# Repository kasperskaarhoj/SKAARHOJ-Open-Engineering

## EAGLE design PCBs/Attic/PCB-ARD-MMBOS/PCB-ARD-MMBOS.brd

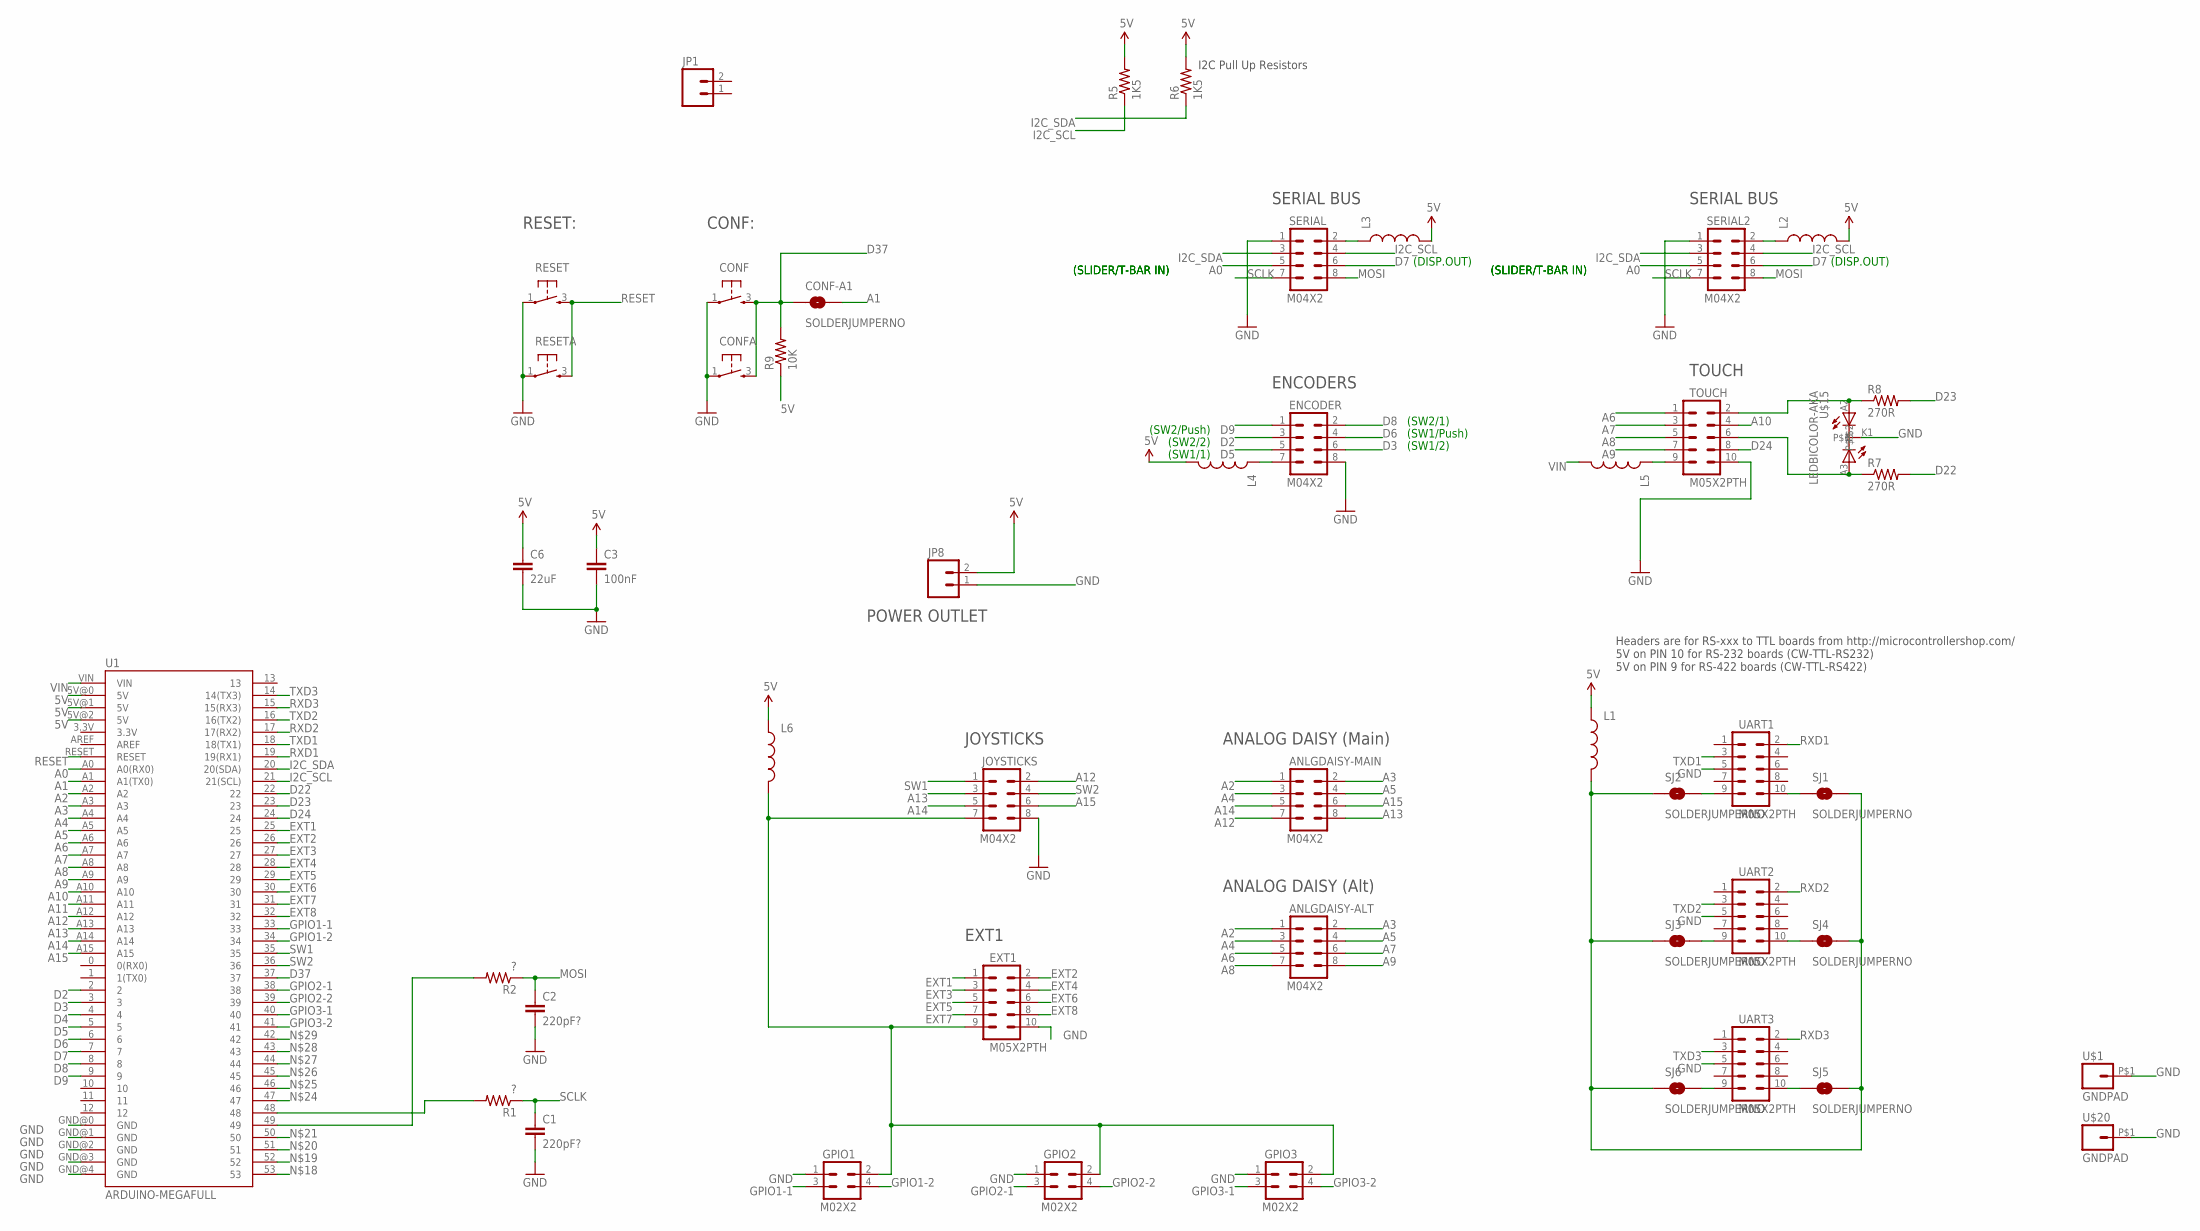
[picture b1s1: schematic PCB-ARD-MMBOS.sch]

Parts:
ANLGDAISY-ALT: M04X2; 2X4
ANLGDAISY-MAIN: M04X2; 2X4
C1, C2: 220pF?; 0603-CAP
C3: 100nF; 0603-CAP
C6: 22uF; 0805
CONF: TAC_SWITCH; PUSHBUTTON
CONF-A1: SOLDERJUMPERNO; SJ_2S-NO
CONFA: TAC_SWITCH; PUSHBUTTON
ENCODER: M04X2; 2X4
EXT1: M05X2PTH; AVR_ICSP
GPIO1, GPIO2, GPIO3: M02X2; 2X2
JOYSTICKS: M04X2; 2X4
JP1: M02PTH; 1X02
JP8: M02PTH4; 1X02_XTRA_BIG
L1, L2, L3, L4, L5, L6: INDUCTOR0805; 0805
R1, R2: ?; 0603-RES
R5, R6: 1K5; 0603-RES
R7, R8: 270R; 0603-RES
R9: 10K; 0603-RES
RESET: TAC_SWITCH; PUSHBUTTON
RESETA: TAC_SWITCH; PUSHBUTTON
SERIAL, SERIAL2: M04X2; 2X4
SJ1, SJ2, SJ3, SJ4, SJ5, SJ6: SOLDERJUMPERNO; SJ_2S-NO
TOUCH: M05X2PTH; AVR_ICSP
U1: ARDUINO-MEGAFULL; ARDUINO_MEGA
U$1, U$20: GNDPAD; 3.2MMPAD
U$15: LEDBICOLOR-AKA; LED5MM-BICOLOR
UART1, UART2, UART3: M05X2PTH; AVR_ICSP

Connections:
5V: C3.1, C6.1, JP8.2, L1.1, L2.2, L3.2, L4.2, L6.1, R5.2, R6.2, R9.1, U1.5V@0 (5V), U1.5V@1 (5V), U1.5V@2 (5V)
A0: SERIAL.5, SERIAL2.5, U1.A0 (A0(RX0))
A1: CONF-A1.2, U1.A1 (A1(TX0))
A2: ANLGDAISY-ALT.1, ANLGDAISY-MAIN.1, U1.A2
A3: ANLGDAISY-ALT.2, ANLGDAISY-MAIN.2, U1.A3
A4: ANLGDAISY-ALT.3, ANLGDAISY-MAIN.3, U1.A4
A5: ANLGDAISY-ALT.4, ANLGDAISY-MAIN.4, U1.A5
A6: ANLGDAISY-ALT.5, TOUCH.1, U1.A6
A7: ANLGDAISY-ALT.6, TOUCH.3, U1.A7
A8: ANLGDAISY-ALT.7, TOUCH.5, U1.A8
A9: ANLGDAISY-ALT.8, TOUCH.7, U1.A9
A10: TOUCH.4, U1.A10
A11: U1.A11
A12: ANLGDAISY-MAIN.7, JOYSTICKS.2, U1.A12
A13: ANLGDAISY-MAIN.8, JOYSTICKS.3, U1.A13
A14: ANLGDAISY-MAIN.5, JOYSTICKS.5, U1.A14
A15: ANLGDAISY-MAIN.6, JOYSTICKS.6, U1.A15
D2: ENCODER.3, U1.2
D3: ENCODER.6, U1.3
D4: U1.4
D5: ENCODER.5, U1.5
D6: ENCODER.4, U1.6
D7: SERIAL.6, SERIAL2.6, U1.7
D8: ENCODER.2, U1.8
D9: ENCODER.1, U1.9
D22: R7.2, U1.22
D23: R8.2, U1.23
D24: TOUCH.8, U1.24
D37: CONF.3, CONF-A1.1, CONFA.3, R9.2, U1.37
EXT1: EXT1.1, U1.25
EXT2: EXT1.2, U1.26
EXT3: EXT1.3, U1.27
EXT4: EXT1.4, U1.28
EXT5: EXT1.5, U1.29
EXT6: EXT1.6, U1.30
EXT7: EXT1.7, U1.31
EXT8: EXT1.8, U1.32
GND: C1.2, C2.2, C3.2, C6.2, CONF.1, CONFA.1, ENCODER.8, EXT1.10, GPIO1.1, GPIO2.1, GPIO3.1, JOYSTICKS.8, JP8.1, RESET.1, RESETA.1, SERIAL.1, SERIAL2.1, TOUCH.10, U1.GND@0 (GND), U1.GND@1 (GND), U1.GND@2 (GND), U1.GND@3 (GND), U1.GND@4 (GND), U$1.P$1, U$15.K1, U$20.P$1, UART1.5, UART2.5, UART3.5
GPIO1-1: GPIO1.3, U1.33
GPIO1-2: GPIO1.4, U1.34
GPIO2-1: GPIO2.3, U1.38
GPIO2-2: GPIO2.4, U1.39
GPIO3-1: GPIO3.3, U1.40
GPIO3-2: GPIO3.4, U1.41
I2C_SCL: R5.1, SERIAL.4, SERIAL2.4, U1.21 (21(SCL))
I2C_SDA: R6.1, SERIAL.3, SERIAL2.3, U1.20 (20(SDA))
MOSI: C2.1, R2.1, SERIAL.8, SERIAL2.8
unnamed: L2.1, SERIAL2.2
unnamed: L3.1, SERIAL.2
unnamed: SJ6.2, UART3.9
unnamed: ENCODER.7, L4.1
unnamed: L5.1, TOUCH.9
unnamed: SJ3.2, UART2.9
unnamed: EXT1.9, GPIO1.2, GPIO2.2, GPIO3.2, JOYSTICKS.7, L6.2
unnamed: L1.2, SJ1.2, SJ2.1, SJ3.1, SJ4.2, SJ5.2, SJ6.1
unnamed: SJ2.2, UART1.9
unnamed: SJ1.1, UART1.10
unnamed: R1.2, U1.48
unnamed: SJ4.1, UART2.10
unnamed: SJ5.1, UART3.10
unnamed: R2.2, U1.49
unnamed: R8.1, TOUCH.2, U$15.A2
unnamed: R7.1, TOUCH.6, U$15.A3
RESET: RESET.3, RESETA.3, U1.RESET
RXD1: U1.19 (19(RX1)), UART1.2
RXD2: U1.17 (17(RX2)), UART2.2
RXD3: U1.15 (15(RX3)), UART3.2
SCLK: C1.1, R1.1, SERIAL.7, SERIAL2.7
SW1: JOYSTICKS.1, U1.35
SW2: JOYSTICKS.4, U1.36
TXD1: U1.18 (18(TX1)), UART1.3
TXD2: U1.16 (16(TX2)), UART2.3
TXD3: U1.14 (14(TX3)), UART3.3
VIN: L5.2, U1.VIN

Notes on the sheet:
JOYSTICKS
EXT1
Headers are for RS-xxx to TTL boards from http://microcontrollershop.com/ 5V on PIN 10 for RS-232 boards (CW-TTL-RS232) 5V on PIN 9 for RS-422 boards (CW-TTL-RS422)
I2C Pull Up Resistors
ENCODERS
SERIAL BUS
TOUCH
(SLIDER/T-BAR IN)
(SW2/Push)
(SW2/2)
(SW1/1)
(SW2/1)
(SW1/Push)
(SW1/2)
(DISP.OUT)
RESET:
CONF:
ANALOG DAISY (Main)
ANALOG DAISY (Alt)
POWER OUTLET

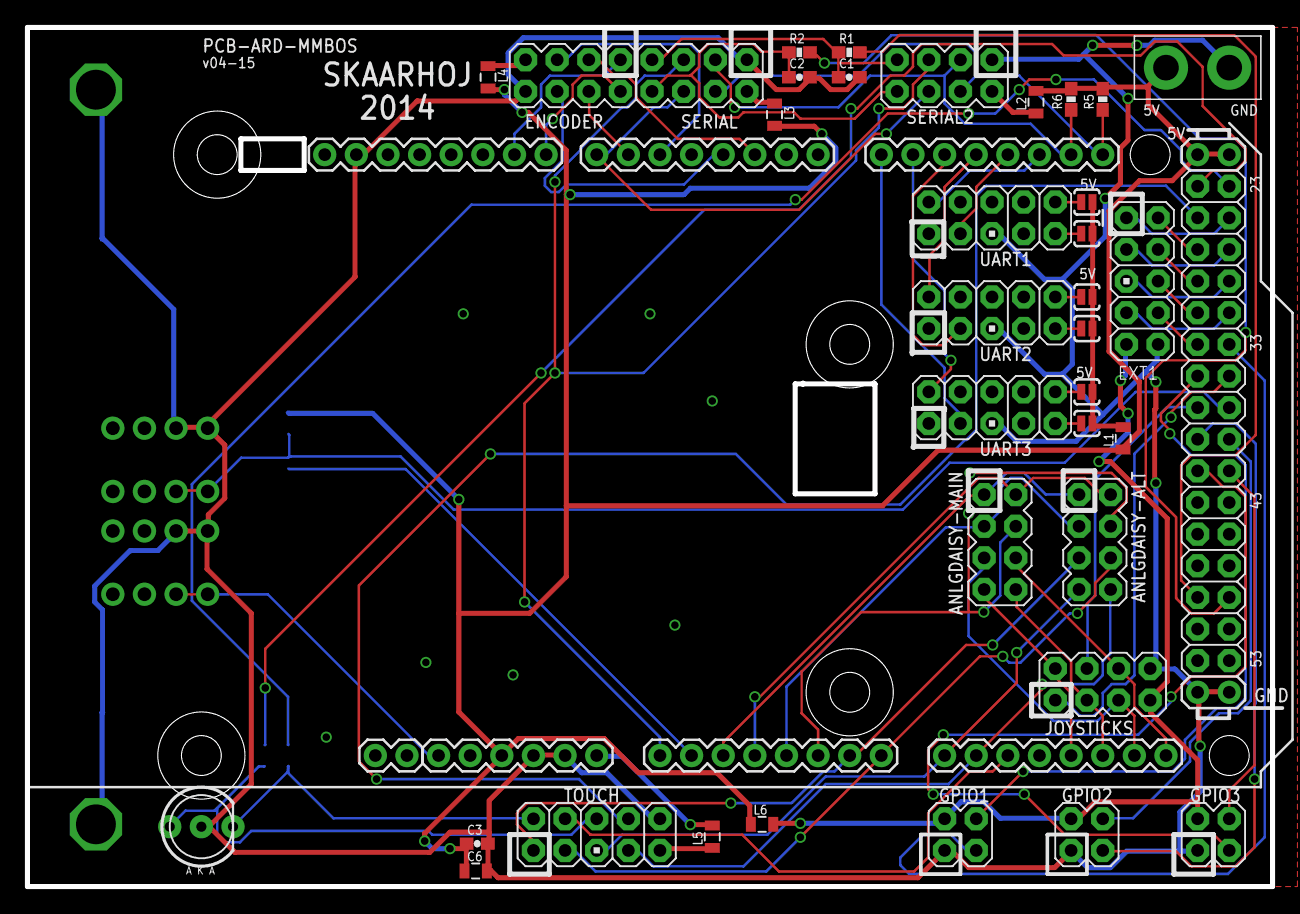
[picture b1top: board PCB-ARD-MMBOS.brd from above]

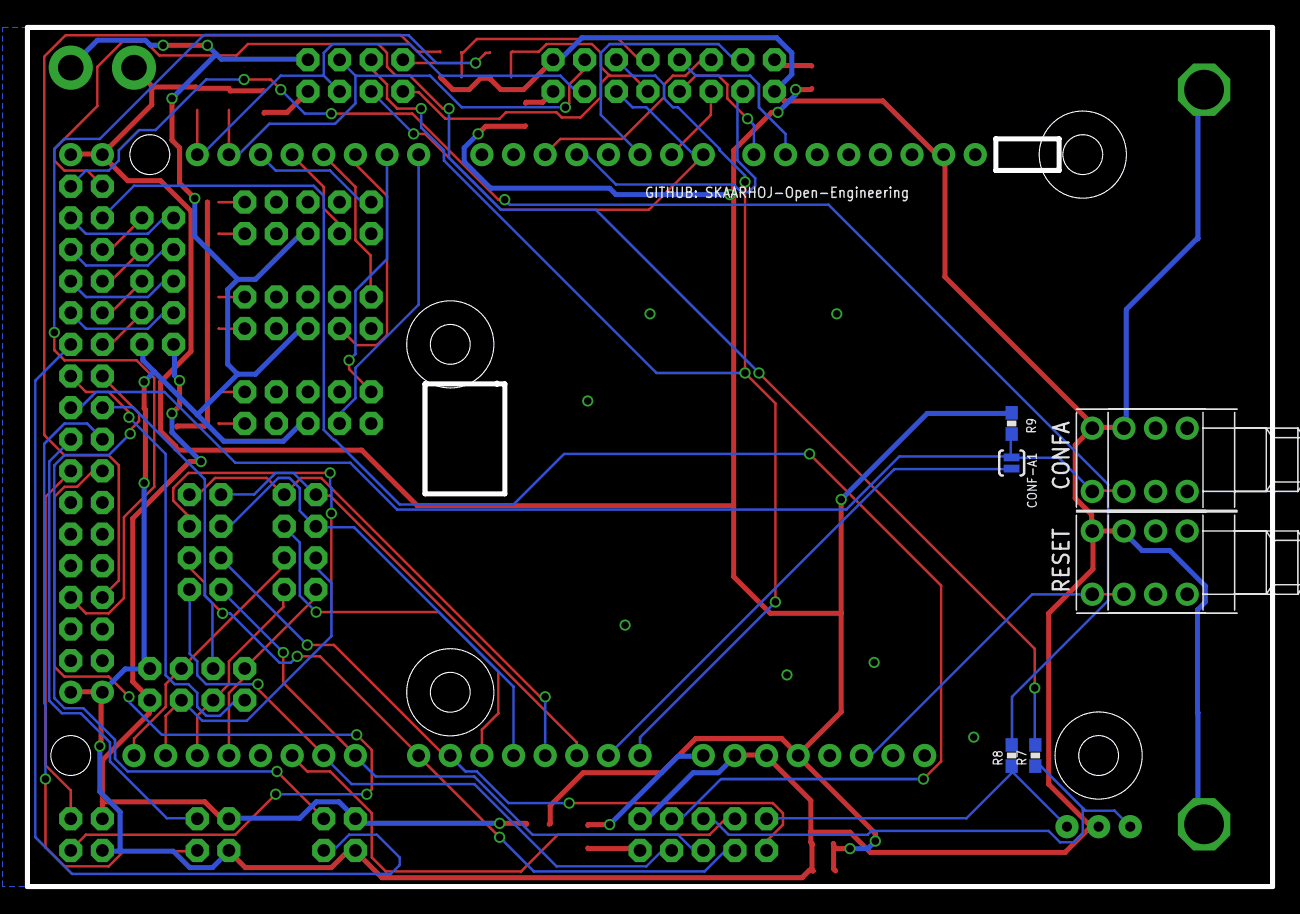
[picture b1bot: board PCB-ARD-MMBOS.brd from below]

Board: 2 copper layers, 100.0 x 69.0 mm, 48 parts (8 on the bottom side), 72 nets.

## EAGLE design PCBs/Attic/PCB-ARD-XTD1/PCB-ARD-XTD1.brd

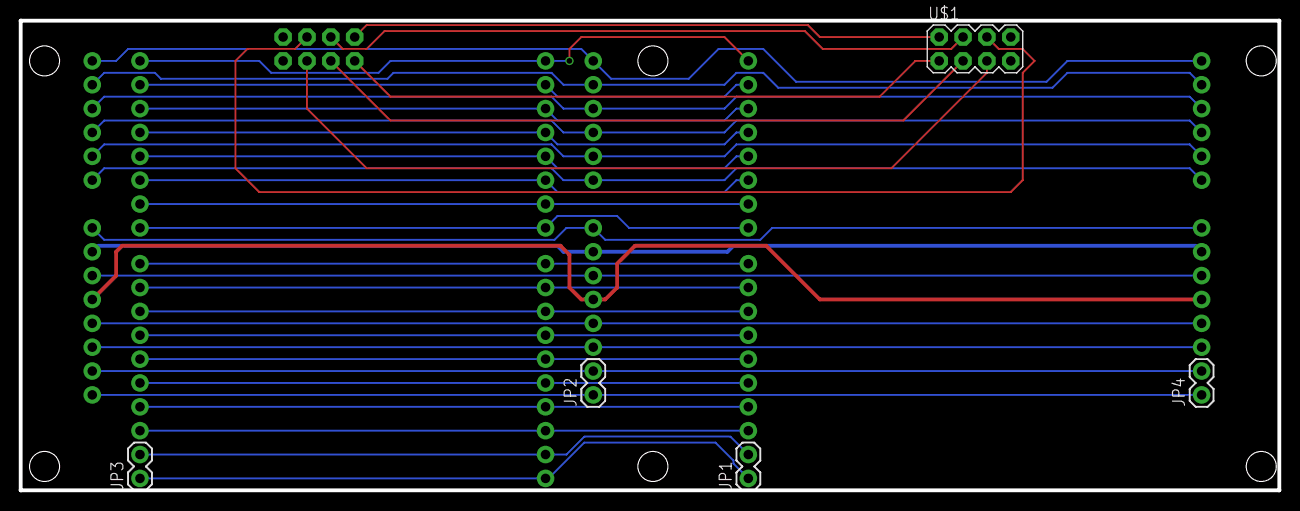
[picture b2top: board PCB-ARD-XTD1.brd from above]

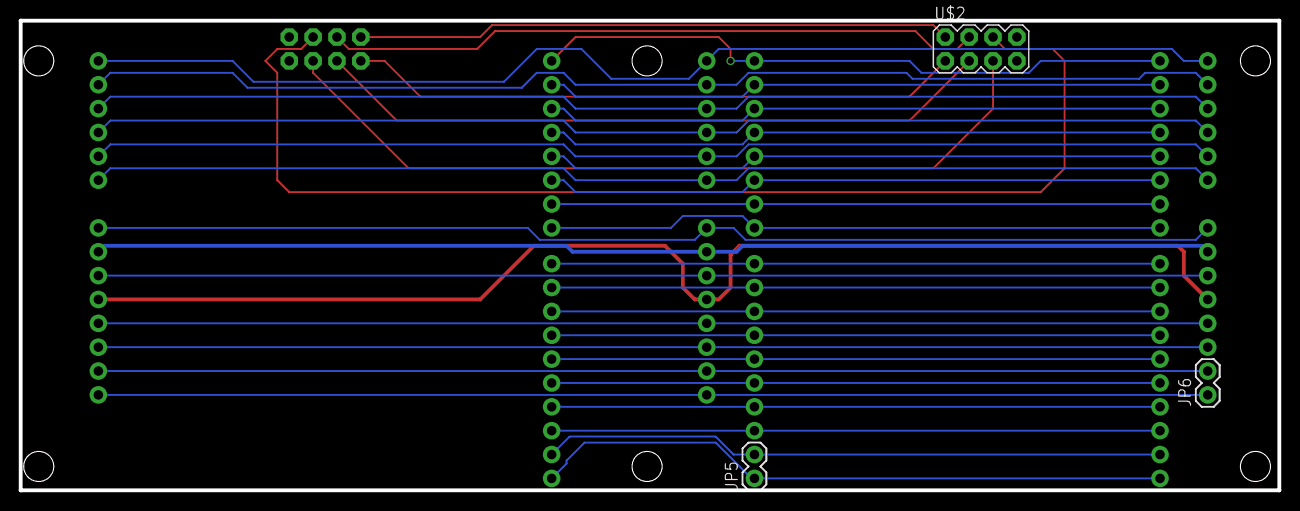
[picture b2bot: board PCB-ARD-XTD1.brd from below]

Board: 2 copper layers, 134.0 x 50.0 mm, 11 parts (4 on the bottom side), 38 nets.

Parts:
JP1, JP2, JP3, JP4, JP5, JP6: 1X02
U1, U2, U3: ARDUINO_SHIELDNO_SILK; DUEMILANOVE_VIAS
U$1, U$2: M04X2; 2X4

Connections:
F1: U1.RX, U2.RX, U3.RX
F2: U1.TX, U2.TX, U3.TX
F3: U1.D2, U2.D2, U3.D2
F4: U1.D3, U2.D3, U3.D3
F5: U1.D4, U2.D4, U3.D4
F6: U1.D5, U2.D5, U3.D5
F7: U1.D6, U2.D6, U3.D6
F8: U1.D7, U2.D7, U3.D7
F9: U1.D8, U2.D8, U3.D8
F10: U1.D9, U2.D9, U3.D9
F11: U1.D10, U2.D10, U3.D10
F12: U1.D11, U2.D11, U3.D11
F13: U1.D12, U2.D12, U3.D12
F14: U1.D13, U2.D13, U3.D13
F15: U1.A0, U2.A0, U3.A0
F16: U1.A1, U2.A1, U3.A1
F17: U1.A2, U2.A2, U3.A2
F18: U1.A3, U2.A3, U3.A3
F19: U1.A4, U2.A4, U3.A4
F20: U1.A5, U2.A5, U3.A5
F21: U1.RES, U2.RES, U3.RES
F22: U1.VIN, U2.VIN, U3.VIN
F23: U1.5V, U2.5V, U3.5V
F24: U1.3.3V, U2.3.3V, U3.3.3V
F25: U1.AREF, U2.AREF, U3.AREF
F26: U1.GND@2, U2.GND@2, U3.GND@2
F27: U1.GND@1, U2.GND@1, U3.GND@1
F28: U1.GND@0, U2.GND@0, U3.GND@0
F29: JP1.2, JP3.2, JP5.2
F30: JP1.1, JP3.1, JP5.1
F31: U$1.1, U$2.1
F32: U$1.3, U$2.3
F33: U$1.5, U$2.5
F35: U$1.2, U$2.2
F36: U$1.4, U$2.4
F37: U$1.6, U$2.6
F39: JP2.2, JP4.2, JP6.2
F40: JP2.1, JP4.1, JP6.1

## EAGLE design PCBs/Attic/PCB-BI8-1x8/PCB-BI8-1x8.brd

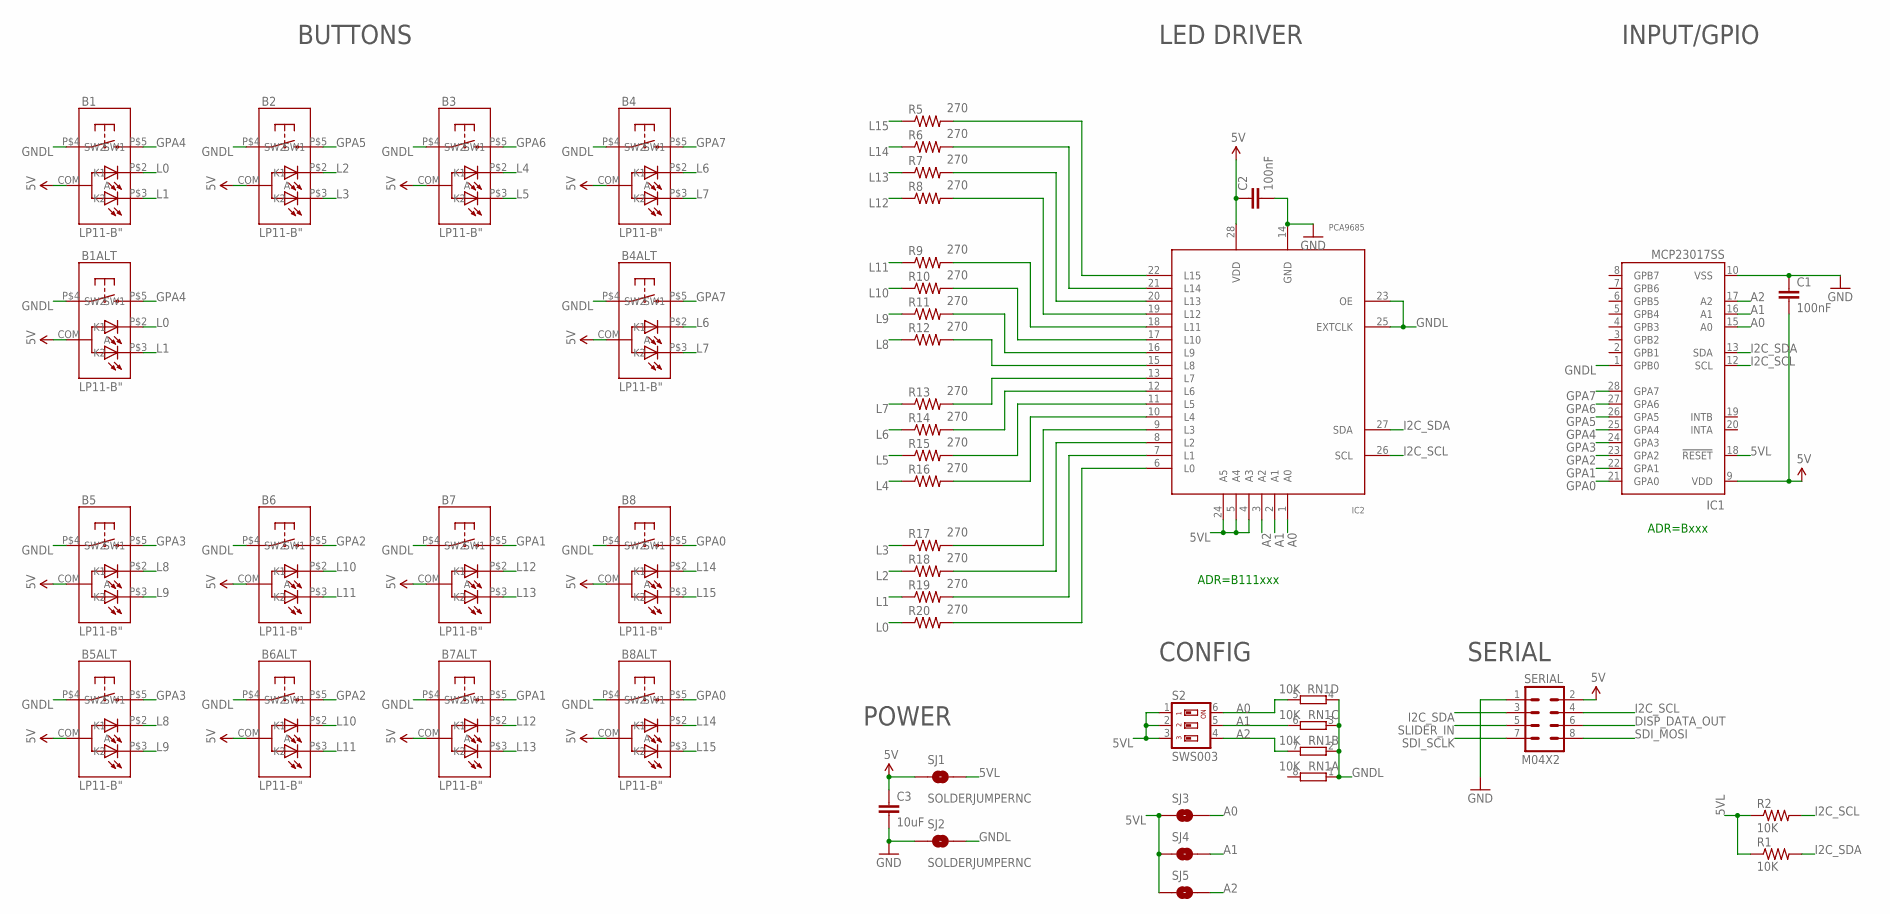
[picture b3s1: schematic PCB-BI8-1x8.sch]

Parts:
B1, B1ALT, B2, B3, B4, B4ALT, B5, B5ALT, B6, B6ALT, B7, B7ALT, B8, B8ALT: LP11-B"; LP11
C1, C2: 100nF; 0603-CAP
C3: 10uF; 0805
IC1: MCP23017SS; SSOP28; MPN MCP23017-E/SS
IC2: PCA9685; TSSOP28
R1, R2: 10K; 0603-RES
R5, R6, R7, R8, R9, R10, R11, R12, R13, R14, R15, R16, R17, R18, R19, R20: 270; 0603-RES
RN1: 10K; CAY16_HAND
S2: SWS003; SMS-003
SERIAL: M04X2; 2X4
SJ1, SJ2, SJ3, SJ4, SJ5: SOLDERJUMPERNC; SJ_2S

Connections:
5V: B1.COM (A), B1ALT.COM (A), B2.COM (A), B3.COM (A), B4.COM (A), B4ALT.COM (A), B5.COM (A), B5ALT.COM (A), B6.COM (A), B6ALT.COM (A), B7.COM (A), B7ALT.COM (A), B8.COM (A), B8ALT.COM (A), C1.2, C2.1, C3.1, IC1.9 (VDD), IC2.28 (VDD), SERIAL.2, SJ1.1
5VL: IC1.18 (!RESET), IC2.4 (A3), IC2.5 (A4), IC2.24 (A5), R1.1, R2.1, S2.1, S2.2, S2.3, SJ1.2, SJ3.1, SJ4.1, SJ5.1
A0: IC1.15 (A0), IC2.1 (A0), RN1.5 (2), S2.6, SJ3.2
A1: IC1.16 (A1), IC2.2 (A1), RN1.6 (2), S2.5, SJ4.2
A2: IC1.17 (A2), IC2.3 (A2), RN1.7 (2), S2.4, SJ5.2
DISP_DATA_OUT: SERIAL.6
GND: C1.1, C2.2, C3.2, IC1.10 (VSS), IC2.14 (GND), SERIAL.1, SJ2.1
GNDL: B1.P$4 (SW1), B1ALT.P$4 (SW1), B2.P$4 (SW1), B3.P$4 (SW1), B4.P$4 (SW1), B4ALT.P$4 (SW1), B5.P$4 (SW1), B5ALT.P$4 (SW1), B6.P$4 (SW1), B6ALT.P$4 (SW1), B7.P$4 (SW1), B7ALT.P$4 (SW1), B8.P$4 (SW1), B8ALT.P$4 (SW1), IC1.1 (GPB0), IC2.23 (OE), IC2.25 (EXTCLK), RN1.1, RN1.2 (1), RN1.3 (1), RN1.4 (1), SJ2.2
GPA0: B8.P$5 (SW2), B8ALT.P$5 (SW2), IC1.21 (GPA0)
GPA1: B7.P$5 (SW2), B7ALT.P$5 (SW2), IC1.22 (GPA1)
GPA2: B6.P$5 (SW2), B6ALT.P$5 (SW2), IC1.23 (GPA2)
GPA3: B5.P$5 (SW2), B5ALT.P$5 (SW2), IC1.24 (GPA3)
GPA4: B1.P$5 (SW2), B1ALT.P$5 (SW2), IC1.25 (GPA4)
GPA5: B2.P$5 (SW2), IC1.26 (GPA5)
GPA6: B3.P$5 (SW2), IC1.27 (GPA6)
GPA7: B4.P$5 (SW2), B4ALT.P$5 (SW2), IC1.28 (GPA7)
I2C_SCL: IC1.12 (SCL), IC2.26 (SCL), R2.2, SERIAL.4
I2C_SDA: IC1.13 (SDA), IC2.27 (SDA), R1.2, SERIAL.3
L0: B1.P$2 (K1), B1ALT.P$2 (K1), R20.1
L1: B1.P$3 (K2), B1ALT.P$3 (K2), R19.1
L2: B2.P$2 (K1), R18.1
L3: B2.P$3 (K2), R17.1
L4: B3.P$2 (K1), R16.1
L5: B3.P$3 (K2), R15.1
L6: B4.P$2 (K1), B4ALT.P$2 (K1), R14.1
L7: B4.P$3 (K2), B4ALT.P$3 (K2), R13.1
L8: B5.P$2 (K1), B5ALT.P$2 (K1), R12.1
L9: B5.P$3 (K2), B5ALT.P$3 (K2), R11.1
L10: B6.P$2 (K1), B6ALT.P$2 (K1), R10.1
L11: B6.P$3 (K2), B6ALT.P$3 (K2), R9.1
L12: B7.P$2 (K1), B7ALT.P$2 (K1), R8.1
L13: B7.P$3 (K2), B7ALT.P$3 (K2), R7.1
L14: B8.P$2 (K1), B8ALT.P$2 (K1), R6.1
L15: B8.P$3 (K2), B8ALT.P$3 (K2), R5.1
unnamed: IC2.13 (L7), R13.2
unnamed: IC2.12 (L6), R14.2
unnamed: IC2.11 (L5), R15.2
unnamed: IC2.10 (L4), R16.2
unnamed: IC2.9 (L3), R17.2
unnamed: IC2.8 (L2), R18.2
unnamed: IC2.7 (L1), R19.2
unnamed: IC2.6 (L0), R20.2
unnamed: IC2.15 (L8), R12.2
unnamed: IC2.16 (L9), R11.2
unnamed: IC2.17 (L10), R10.2
unnamed: IC2.18 (L11), R9.2
unnamed: IC2.19 (L12), R8.2
unnamed: IC2.20 (L13), R7.2
unnamed: IC2.21 (L14), R6.2
unnamed: IC2.22 (L15), R5.2
SDI_MOSI: SERIAL.8
SDI_SCLK: SERIAL.7
SLIDER_IN: SERIAL.5

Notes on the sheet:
ADR=B111xxx
ADR=Bxxx
BUTTONS
LED DRIVER
INPUT/GPIO
POWER
CONFIG
SERIAL

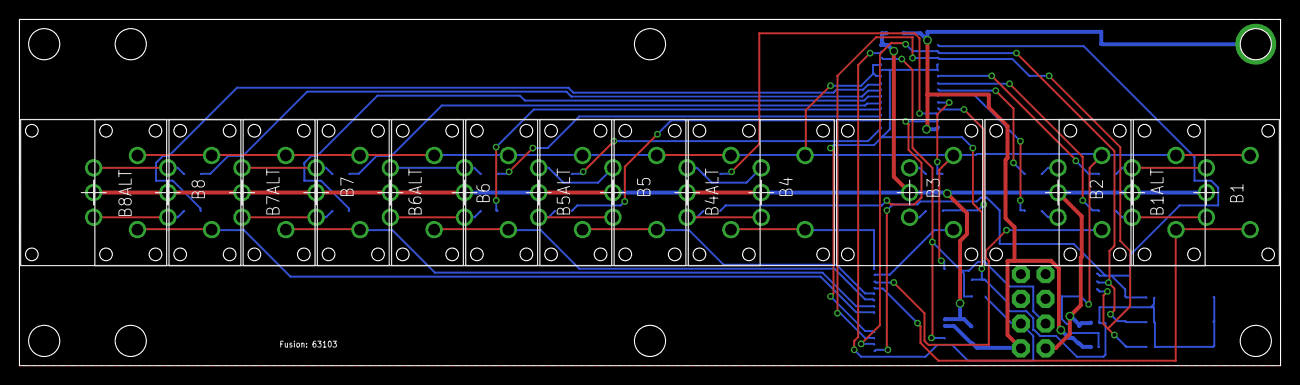
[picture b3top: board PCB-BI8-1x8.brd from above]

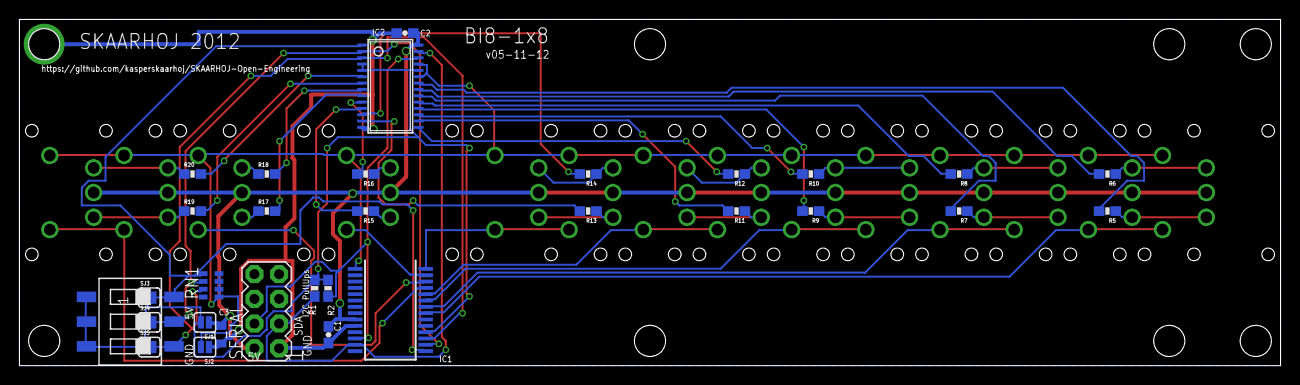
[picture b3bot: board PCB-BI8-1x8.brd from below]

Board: 2 copper layers, 129.5 x 35.6 mm, 45 parts (31 on the bottom side), 49 nets.

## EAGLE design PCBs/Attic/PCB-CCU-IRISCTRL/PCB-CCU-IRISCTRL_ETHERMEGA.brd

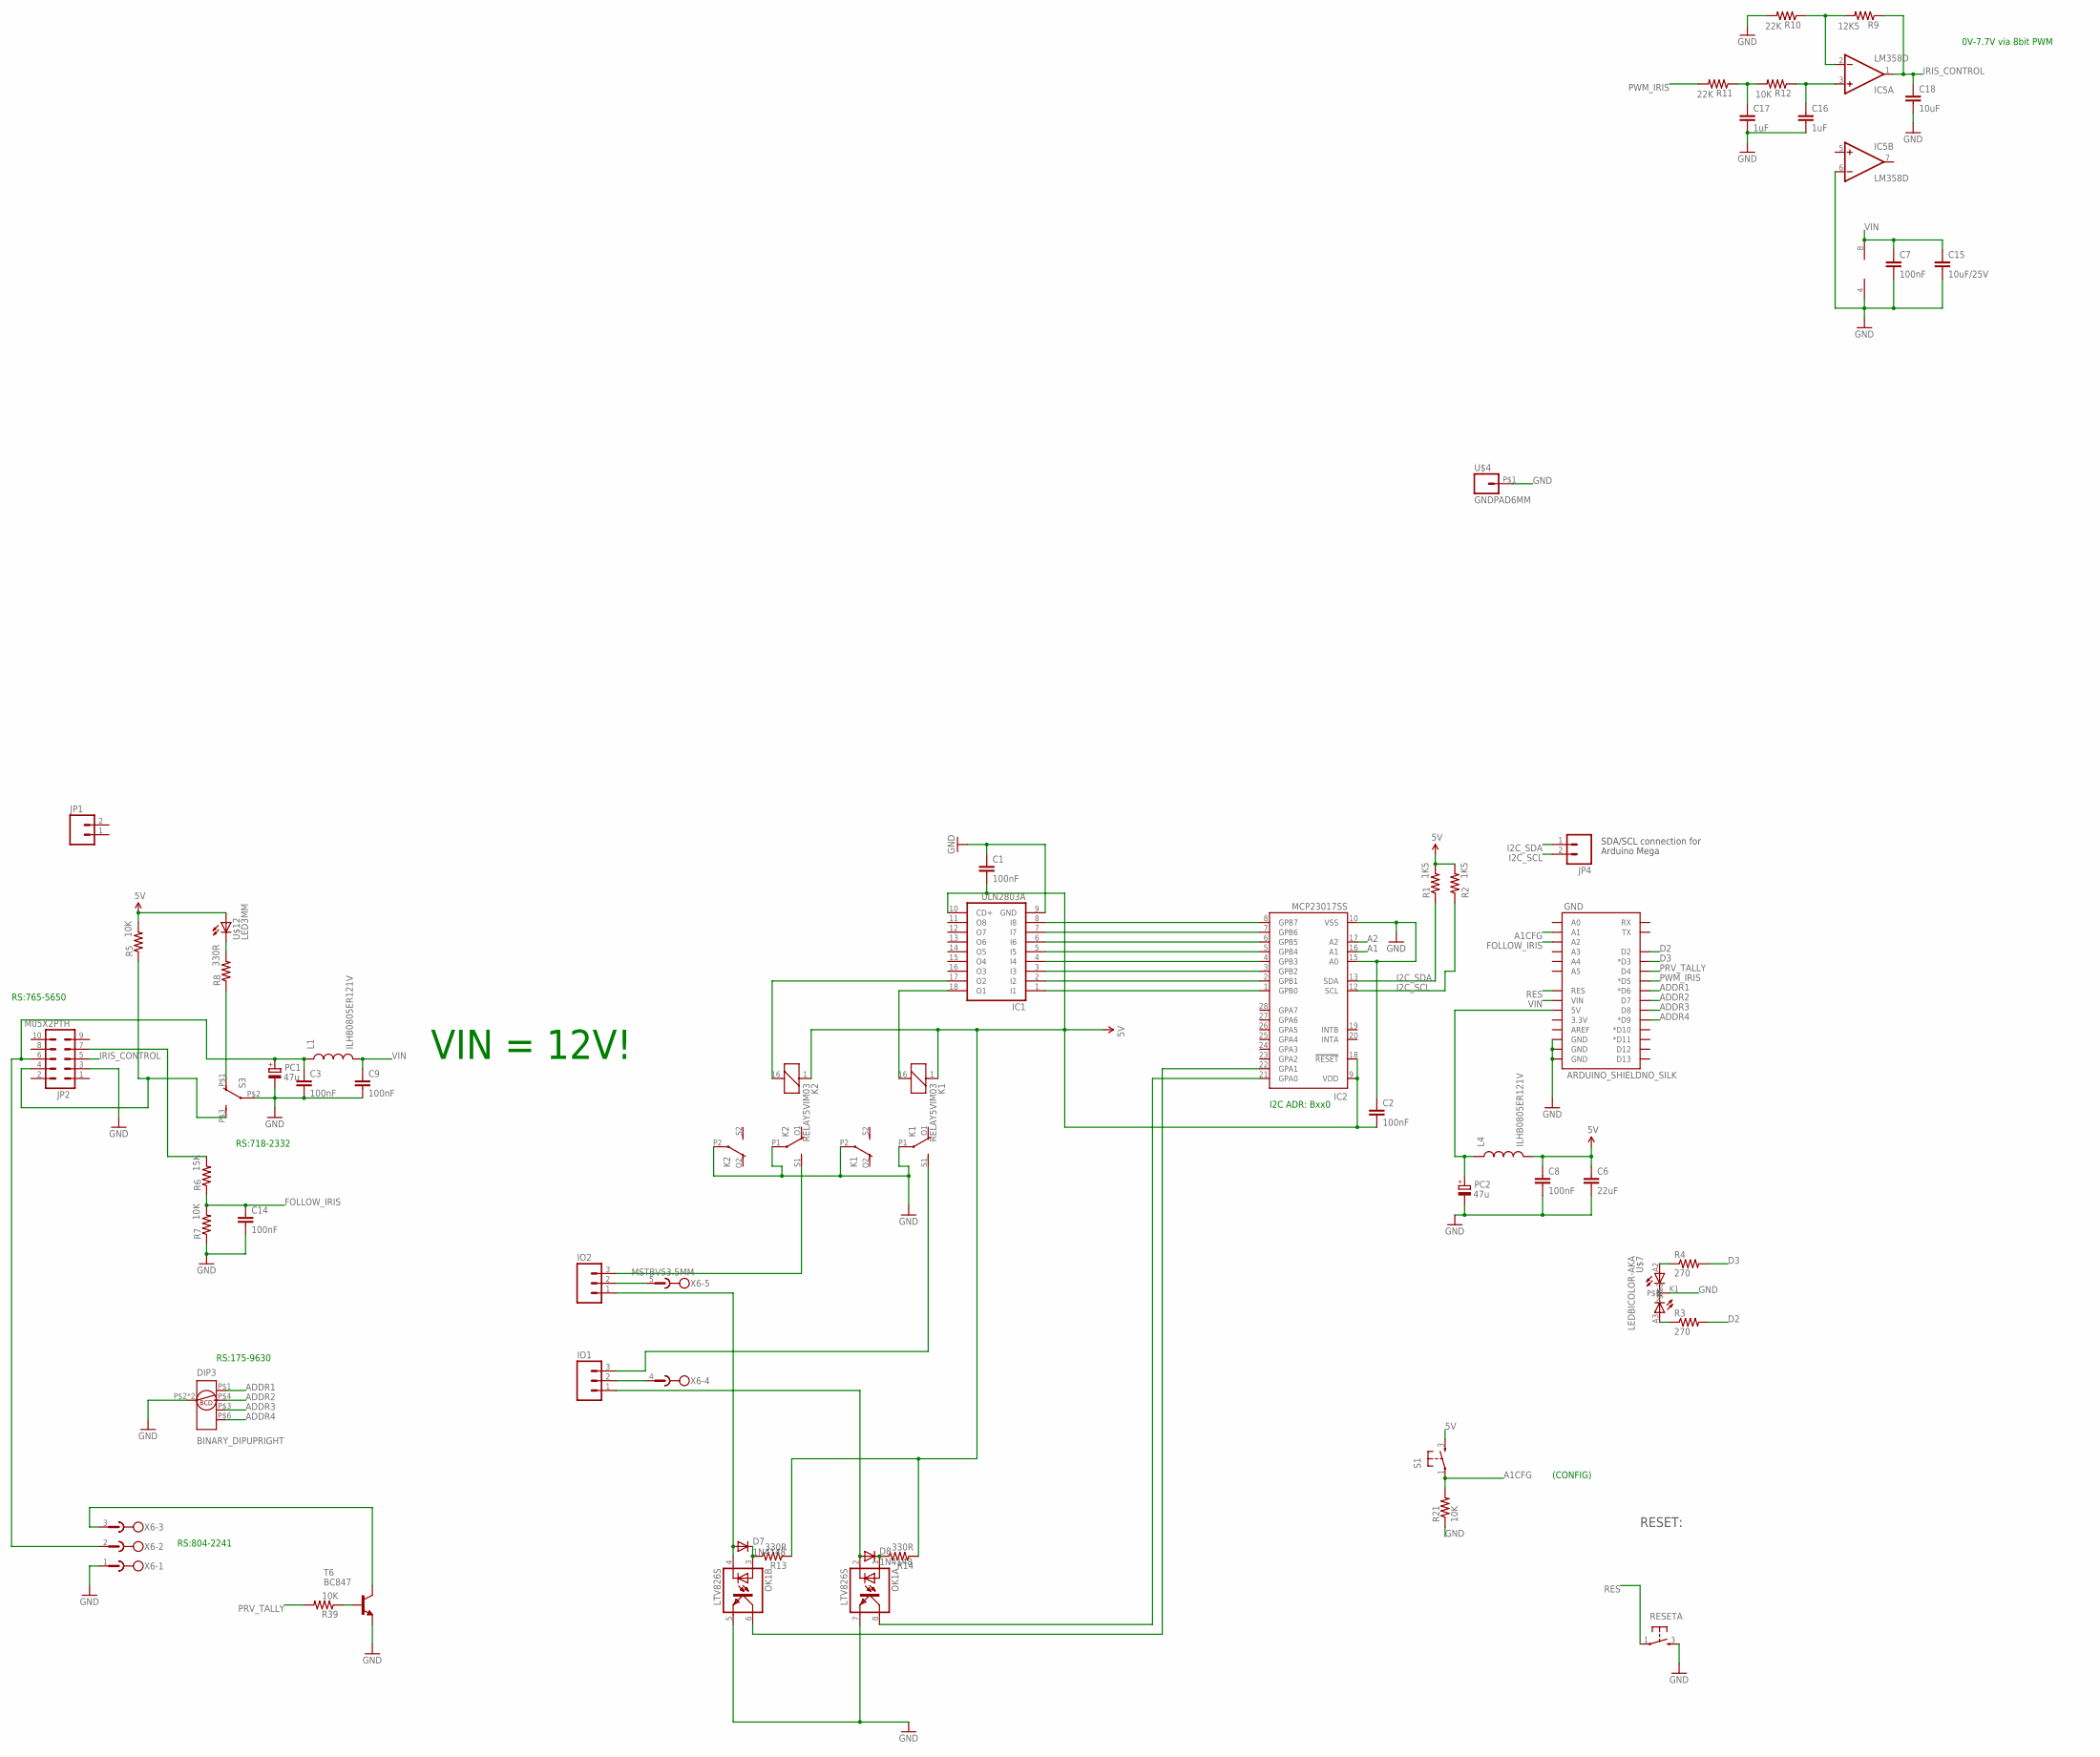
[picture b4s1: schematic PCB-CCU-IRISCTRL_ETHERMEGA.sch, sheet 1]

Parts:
C1: 100nF; 0805
C2, C3, C7, C8, C9, C14: 100nF; 0603-CAP
C6: 22uF; 0805
C15: 10uF/25V; 0805
C16, C17: 1uF; 0805
C18: 10uF; 0805
D7, D8: 1N4148; SOD-323
DIP3: BINARY_DIPUPRIGHT; P65SMT_UPRIGHT_TH
GND: ARDUINO_SHIELDNO_SILK; DUEMILANOVE_VIAS
IC1: ULN2803A; SO18W
IC2: MCP23017SS; SSOP28
IC5: LM358D; SO08
IO1, IO2: M03LOCK; 1X03_LOCK
JP1, JP4: M02PTH; 1X02
JP2: M05X2PTH; AVR_ICSP
K1, K2: RELAY5VIM03; DS2Y
L1, L4: ILHB0805ER121V; 0805
OK1: LTV826S; DIL8-SMD
PC1, PC2: 47u; PANASONIC_D
R1, R2: 1K5; 0603-RES
R3, R4: 270; 0603-RES
R5, R7, R12, R21, R39: 10K; 0603-RES
R6: 15K; 0603-RES
R8, R13, R14: 330R; 0603-RES
R9: 12K5; 0603-RES
R10, R11: 22K; 0603-RES
RESETA: TAC_SWITCH; PUSHBUTTON
S1: TAC_SWITCH; PUSHBUTTON
S3: SWITCH-DPST; TECONNECTIVITY-DPST
T6: BC847; SOT23
U$4: GNDPAD6MM; 3.2MMPAD6MM
U$7: LEDBICOLOR-AKA; LED5MM-BICOLOR
U$12: LED3MM
X6: MSTBV53.5MM; MSTBV5-3.5

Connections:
5V: C1.2, C2.2, C6.1, C8.1, IC1.10 (CD+), IC2.9 (VDD), IC2.18 (!RESET), K1.1, K2.1, L4.2, R1.2, R2.2, R5.2, R13.1, R14.1, S1.3, U$12.A
A1: IC2.16 (A1)
A1CFG: GND.A1, R21.2, S1.1
A2: IC2.17 (A2)
ADDR1: DIP3.P$1 (1), GND.D6 (*D6)
ADDR2: DIP3.P$4 (2), GND.D7
ADDR3: DIP3.P$3 (4), GND.D8
ADDR4: DIP3.P$6 (8), GND.D9 (*D9)
ARD_5V: GND.5V, L4.1, PC2.+
D2: GND.D2, R3.2
D3: GND.D3 (*D3), R4.2
FOLLOW_IRIS: C14.1, GND.A2, R6.1, R7.2
GND: C1.1, C2.1, C3.2, C6.2, C7.2, C8.2, C9.2, C14.2, C15.2, C16.2, C17.2, C18.2, DIP3.P$2 (GND), DIP3.P$5 (GND), GND.GND@0 (GND), GND.GND@1 (GND), GND.GND@2 (GND), IC1.9 (GND), IC2.10 (VSS), IC2.15 (A0), IC5.4 (V-), IC5.6 (-IN), JP2.3, K1.P1, K1.P2, K2.P1, K2.P2, OK1.5 (EMIT), OK1.7 (EMIT), PC1.-, PC2.-, R7.1, R10.2, R21.1, RESETA.3, S3.P$2, T6.2 (E), U$4.P$1, U$7.K1, X6.1
I2C_SCL: IC2.12 (SCL), JP4.2, R2.1
I2C_SDA: IC2.13 (SDA), JP4.1, R1.1
IRIS_CONTROL: C18.1, IC5.1 (OUT), JP2.5, R9.1
unnamed: IO2.3, K2.S1 (S)
unnamed: IC1.18 (O1), K1.16 (2)
unnamed: IC1.1 (I1), IC2.1 (GPB0)
unnamed: IO2.2, X6.5
unnamed: R4.1, U$7.A2
unnamed: IC1.17 (O2), K2.16 (2)
unnamed: IO1.3, K1.S1 (S)
unnamed: R3.1, U$7.A3
unnamed: IO1.2, X6.4
unnamed: R39.1, T6.1 (B)
unnamed: JP2.7, R6.2
unnamed: R8.1, S3.P$1 (O)
unnamed: C3.1, JP2.6, L1.1, PC1.+, X6.2
unnamed: R8.2, U$12.K (C)
unnamed: C17.1, R11.1, R12.2
unnamed: C16.1, IC5.3 (+IN), R12.1
unnamed: IC5.2 (-IN), R9.2, R10.1
unnamed: IC1.2 (I2), IC2.2 (GPB1)
unnamed: IC1.3 (I3), IC2.3 (GPB2)
unnamed: IC1.4 (I4), IC2.4 (GPB3)
unnamed: IC1.5 (I5), IC2.5 (GPB4)
unnamed: IC1.6 (I6), IC2.6 (GPB5)
unnamed: IC1.7 (I7), IC2.7 (GPB6)
unnamed: IC1.8 (I8), IC2.8 (GPB7)
unnamed: D7.1 (C), OK1.3 (A), R13.2
unnamed: D8.1 (C), OK1.1 (A), R14.2
unnamed: D8.2 (A), IO1.1, OK1.2 (C)
unnamed: IC2.21 (GPA0), OK1.8 (COL)
unnamed: D7.2 (A), IO2.1, OK1.4 (C)
unnamed: IC2.22 (GPA1), OK1.6 (COL)
PRV_TALLY: GND.D4, R39.2
PWM_IRIS: GND.D5 (*D5), R11.2
RES: GND.RES, RESETA.1
RESET: T6.3 (C), X6.3
VIN: C7.1, C9.1, C15.1, GND.VIN, IC5.8 (V+), L1.2
_IRIS_MANUAL: JP2.4, R5.1, S3.P$3 (S)

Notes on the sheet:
I2C ADR: Bxx0
SDA/SCL connection for
Arduino Mega
(CONFIG)
RESET:
VIN = 12V!
RS:175-9630
RS:718-2332
RS:804-2241
RS:765-5650
0V-7.7V via 8bit PWM

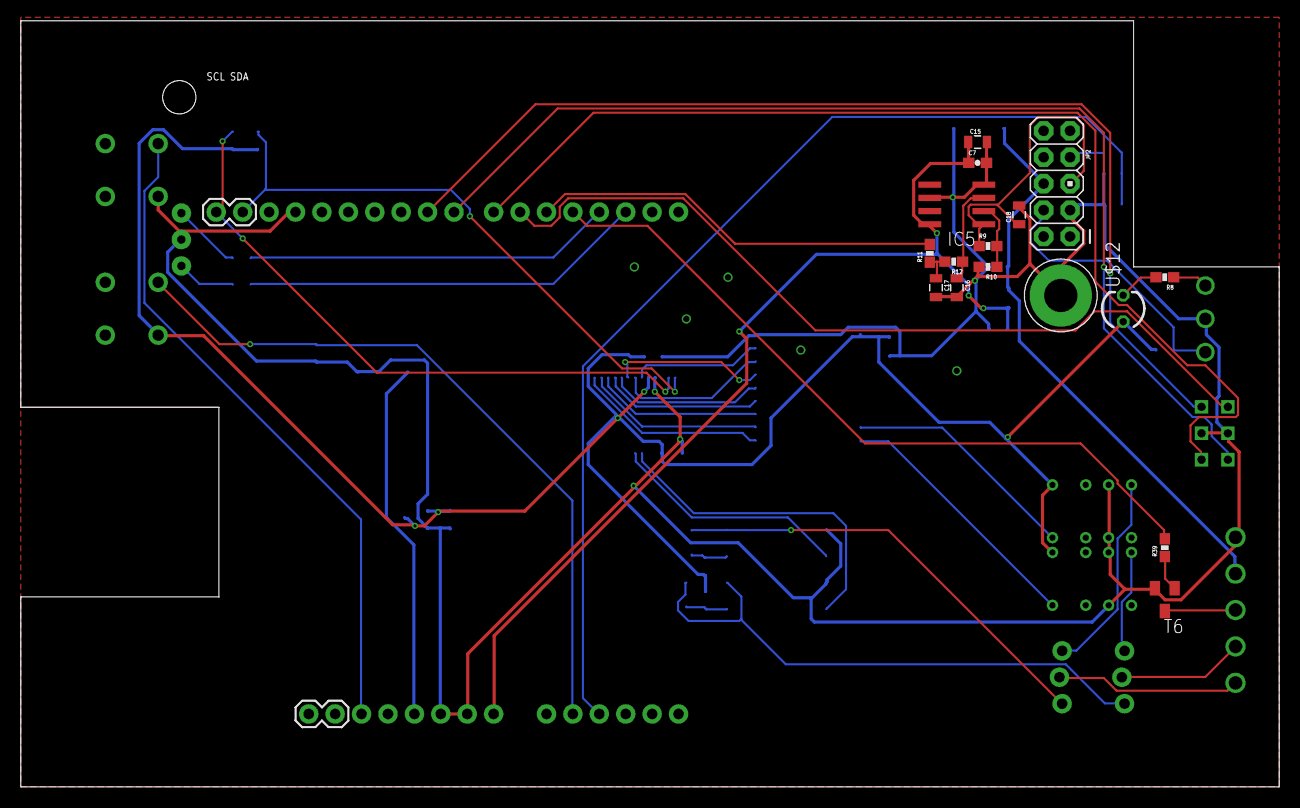
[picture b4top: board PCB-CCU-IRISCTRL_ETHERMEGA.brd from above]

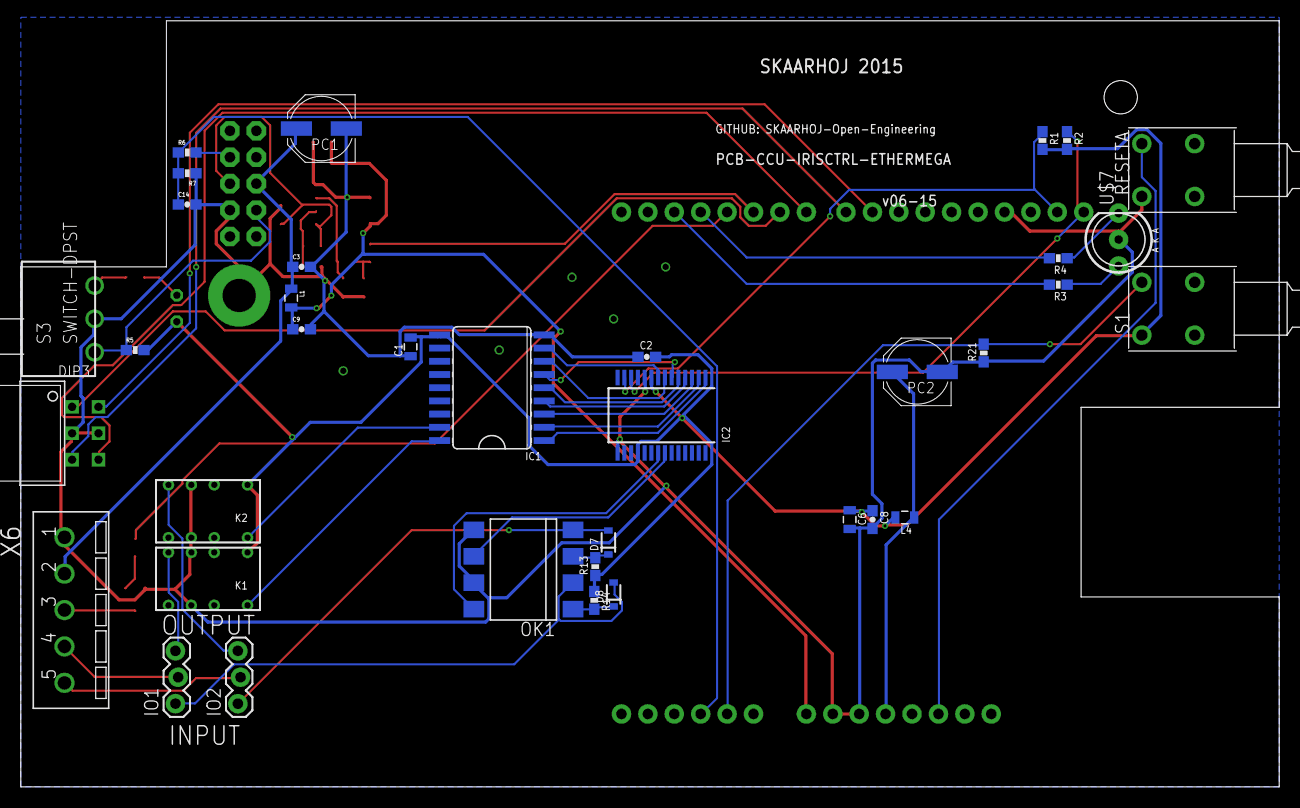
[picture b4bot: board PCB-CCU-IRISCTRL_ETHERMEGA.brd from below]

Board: 2 copper layers, 121.0 x 73.7 mm, 55 parts (36 on the bottom side), 50 nets.

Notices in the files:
parts and their libraries:
SparkFun: Licensing: CC v3.0 Share-Alike You are welcome to use this library for commercial purposes.
